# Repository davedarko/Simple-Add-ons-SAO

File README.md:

# Simple-Add-ons-SAO
Hardware Conference Badges tend to turn very complex, so to allow people to add bling and memes to their badge, the SAO (then shitty add-on) standard was developed. It started as a 2x2 header with two power pins and two I2C pins for data and a clock signal. Let me introduce you to the standard and show you what can be achieved. This is one of my favorite things to design, as they can be nice little gifts and inspires a lot of people for future years to also design and gift some. 

They are perfect gifts and spark joy!

Find all of my ~~shitty~~ simple add-ons in this repository. Plus some badges that were never converted to SAO but they still blink and everything.

## The current header - V1.69bis
The header was expanded to a 2x3 ISP connector later. Looking at the simple add-on, this is the layout.

## Designs in this repository

|Badge Name| Type | Eagle | Kicad | Description |
|----------|------|-------|-------|-------------|
| Ghibli/Soot Sprites | SAO | yes | - | A susuwatari simple add-on |
| LECCO postcard  | SAO | yes | - | Reminder token for a good time at Hackaday Europe 2026 in Lecco, Italy |
| Han SAOlo in carbonyte  | SAO | - | yes | work in progress, Attiny202 with RGB LEDs https://hackaday.io/project/197803-han-saolo|
| COVID-19 badge | SAO | - | yes | blinks with the help of a 555 timer on the back https://hackaday.io/project/187615-covid-19-sao-simple-add-on |
| "Hello my name is"  | SAO | - | yes | some blinks, some no https://hackaday.io/project/197693-hello-my-name-is-sao |
| MrAnderson  | SAO | - | yes | work in progress, hommage to Andy Anderson |
| Vendetta badge | SAO | - | yes | "remember, remember the 5th of November" - or anything else with the help of the little EEPROM on the back of this badge |
| Mr. Robot | SAO | yes | yes | with Attiny speaker https://hackaday.io/project/168037-mr-robot-shitty-addon |
| Penghito Poco | SAO | yes | - | small penghicorn badge |
| Do Or Donut | SAO | yes | - |  LED sprinkle matrix https://hackaday.io/project/168597-do-or-donut-sao |
| Knight Rider badge | SAO / pin | yes | yes | K.I.T.T. with animations thanks to an Attiny13 https://hackaday.io/project/25944-kitt-knight-rider-badgebrooch |
| sloth badge | pin | yes | - | inspired by some cute pimoroni pins, a sloth badge was formed https://hackaday.io/project/28330-sloth-badge |
| flux capacitor | pin | yes | - | with animations thanks to an Attiny13, the flux is flowing https://hackaday.io/project/25898-flux-capacitor-trinket|
| retro spacehuhn badge | pin | yes | - | RGB LED eyes on an olg Spacehuhn logo, with markers used for multicolor PCBs https://hackaday.io/project/33886-spacehuhn-badge |
| library stick  | other | yes | - | show off all your simple add-ons |

## Further designs

|Badge Name| Type | Eagle | Kicad | Description |
|----------|------|-------|-------|-------------|
| YoDawgSAO | SAO| - | yes| I heard you like badges on your badges? Here have some badges for your badges for your badges! https://github.com/davedarko/YoDawgSAO |
| T.A.R.S. | SAO| - | yes| Probably my most complex design, a small TARS with display and RP2040 https://github.com/davedarko/TARS-SAO |

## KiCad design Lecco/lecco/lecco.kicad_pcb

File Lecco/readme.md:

# Lecco, IT

First of all I'm so sorry for the footprint fail - the guy who gave a talk on how not to eff up the footprint, did exactly that, after making a whole bunch off addons.

You basically need an LED and a simple 2 row SMD header to make this work, but you have to botch the LED on it somehow.

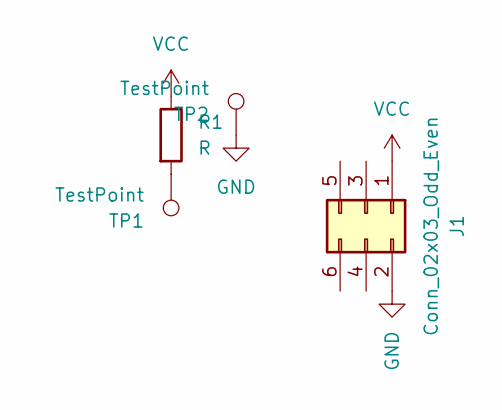
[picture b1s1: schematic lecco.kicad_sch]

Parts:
J1: Conn_02x03_Odd_Even; PinSocket_2x03_P2.54mm_Vertical_SMD
R1: R; R_0603_1608Metric_Pad0.98x0.95mm_HandSolder
TP1, TP2: TestPoint; TestPoint_Pad_D2.0mm

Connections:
GND: J1.2, TP2.1
unnamed: R1.2, TP1.1
VCC: J1.1, R1.1

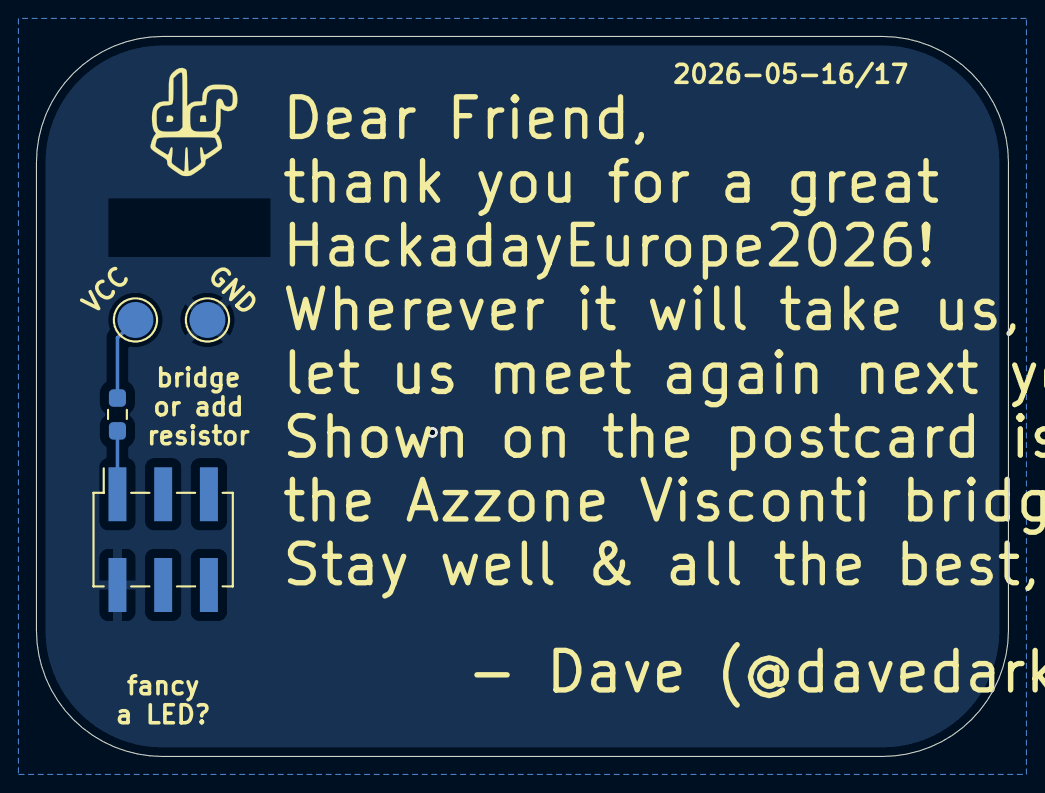
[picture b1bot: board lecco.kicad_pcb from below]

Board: 2 copper layers, 54.0 x 40.0 mm, 5 parts (5 on the bottom side), 3 nets.

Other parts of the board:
Ref**: Val**; davedarko_logo_silk_outline

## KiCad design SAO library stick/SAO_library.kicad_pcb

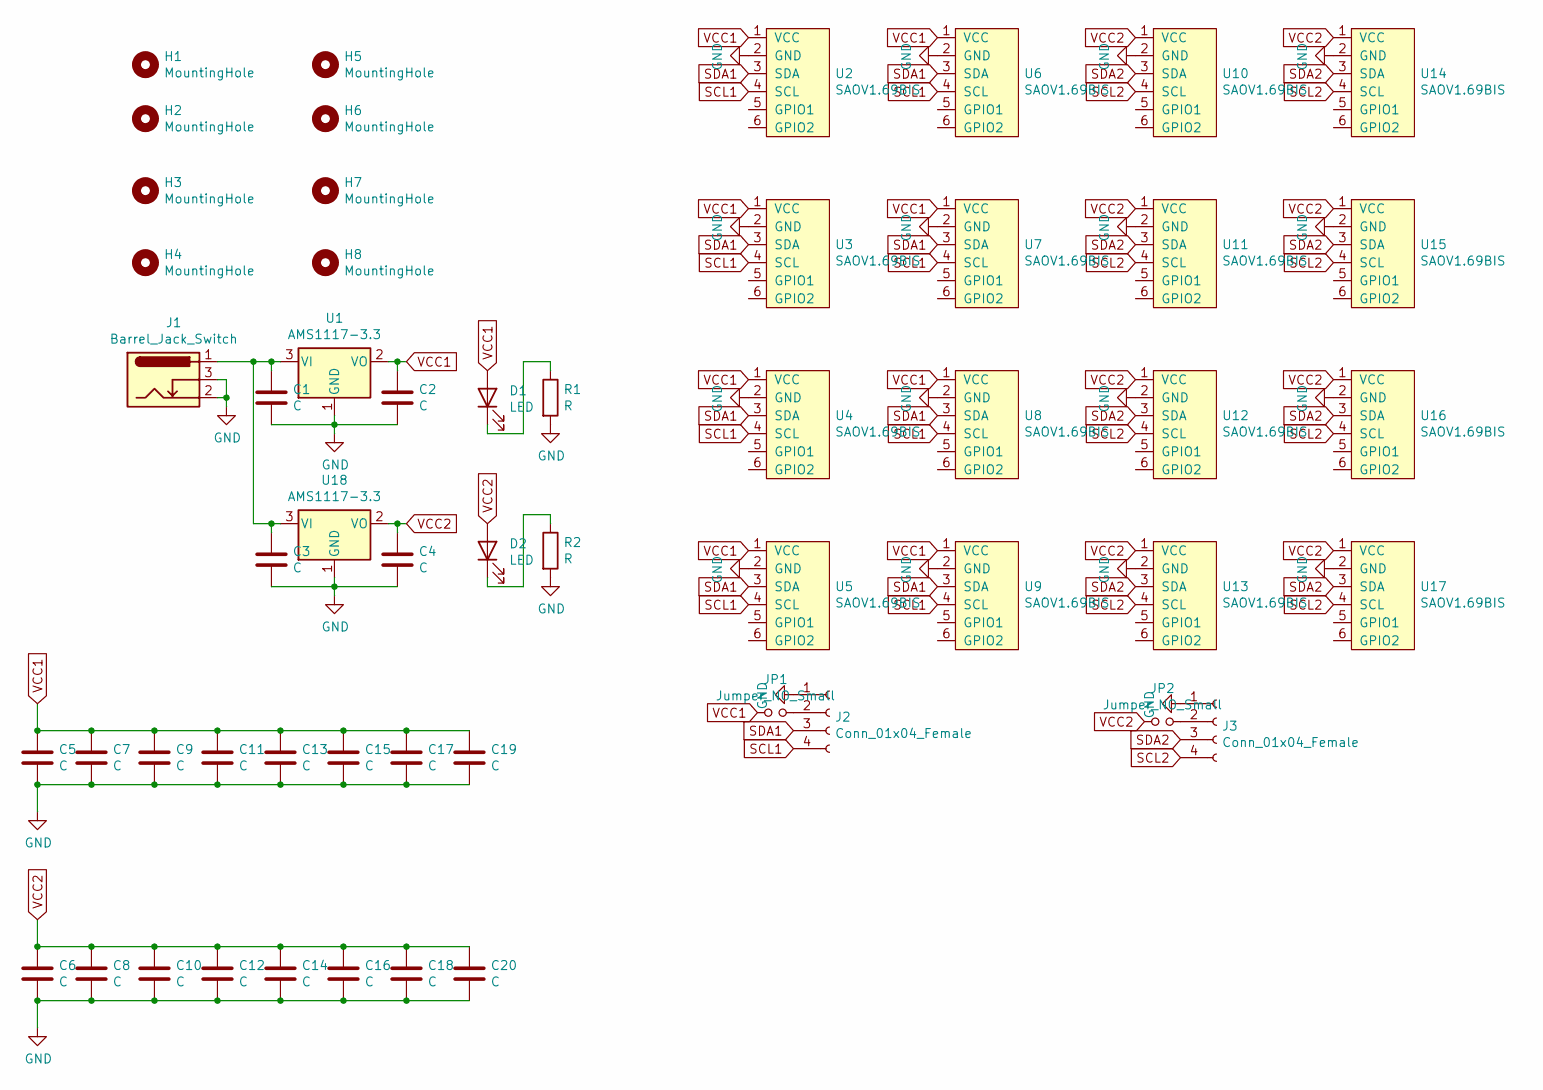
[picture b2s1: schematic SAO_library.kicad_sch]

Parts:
C1, C2, C3, C4, C5, C6, C7, C8, C9, C10, C11, C12, C13, C14, C15, C16, C17, C18, C19, C20: C; C_1206_3216Metric_Pad1.33x1.80mm_HandSolder
D1, D2: LED; LED_1206_3216Metric
H1, H2, H3, H4, H5, H6, H7, H8: MountingHole; MountingHole_3.2mm_M3_Pad_Via
J1: Barrel_Jack_Switch; BarrelJack_CUI_PJ-102AH_Horizontal
J2, J3: Conn_01x04_Female; JST_SH_SM04B-SRSS-TB_1x04-1MP_P1.00mm_Horizontal
JP1, JP2: Jumper_NO_Small; SolderJumper-2_P1.3mm_Open_RoundedPad1.0x1.5mm
R1, R2: R; R_1206_3216Metric_Pad1.30x1.75mm_HandSolder
U1, U18: AMS1117-3.3; SOT-223-3_TabPin2
U2, U3, U4, U5, U6, U7, U8, U9, U10, U11, U12, U13, U14, U15, U16, U17: SAOV1.69BIS; PinSocket_2x03_P2.54mm_Vertical

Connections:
GND: C1.2, C2.2, C3.2, C4.2, C5.2, C6.2, C7.2, C8.2, C9.2, C10.2, C11.2, C12.2, C13.2, C14.2, C15.2, C16.2, C17.2, C18.2, C19.2, C20.2, J1.2, J1.3, J2.1, J3.1, R1.2, R2.2, U1.1 (GND), U2.2 (GND), U3.2 (GND), U4.2 (GND), U5.2 (GND), U6.2 (GND), U7.2 (GND), U8.2 (GND), U9.2 (GND), U10.2 (GND), U11.2 (GND), U12.2 (GND), U13.2 (GND), U14.2 (GND), U15.2 (GND), U16.2 (GND), U17.2 (GND), U18.1 (GND)
unnamed: C1.1, C3.1, J1.1, U1.3 (VI), U18.3 (VI)
unnamed: D1.1 (K), R1.1
unnamed: D2.1 (K), R2.1
unnamed: J2.2, JP1.2
unnamed: J3.2, JP2.2
SCL1: J2.4, U2.4 (SCL), U3.4 (SCL), U4.4 (SCL), U5.4 (SCL), U6.4 (SCL), U7.4 (SCL), U8.4 (SCL), U9.4 (SCL)
SCL2: J3.4, U10.4 (SCL), U11.4 (SCL), U12.4 (SCL), U13.4 (SCL), U14.4 (SCL), U15.4 (SCL), U16.4 (SCL), U17.4 (SCL)
SDA1: J2.3, U2.3 (SDA), U3.3 (SDA), U4.3 (SDA), U5.3 (SDA), U6.3 (SDA), U7.3 (SDA), U8.3 (SDA), U9.3 (SDA)
SDA2: J3.3, U10.3 (SDA), U11.3 (SDA), U12.3 (SDA), U13.3 (SDA), U14.3 (SDA), U15.3 (SDA), U16.3 (SDA), U17.3 (SDA)
VCC1: C2.1, C5.1, C7.1, C9.1, C11.1, C13.1, C15.1, C17.1, C19.1, D1.2 (A), JP1.1, U1.2 (VO), U2.1 (VCC), U3.1 (VCC), U4.1 (VCC), U5.1 (VCC), U6.1 (VCC), U7.1 (VCC), U8.1 (VCC), U9.1 (VCC)
VCC2: C4.1, C6.1, C8.1, C10.1, C12.1, C14.1, C16.1, C18.1, C20.1, D2.2 (A), JP2.1, U10.1 (VCC), U11.1 (VCC), U12.1 (VCC), U13.1 (VCC), U14.1 (VCC), U15.1 (VCC), U16.1 (VCC), U17.1 (VCC), U18.2 (VO)

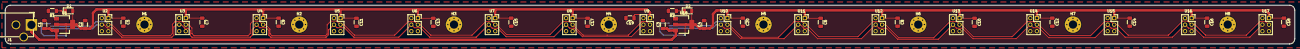
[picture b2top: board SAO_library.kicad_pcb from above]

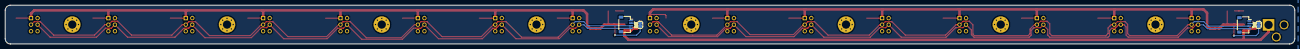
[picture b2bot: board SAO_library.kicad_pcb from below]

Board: 2 copper layers, 500.0 x 15.0 mm, 55 parts (4 on the bottom side), 12 nets.

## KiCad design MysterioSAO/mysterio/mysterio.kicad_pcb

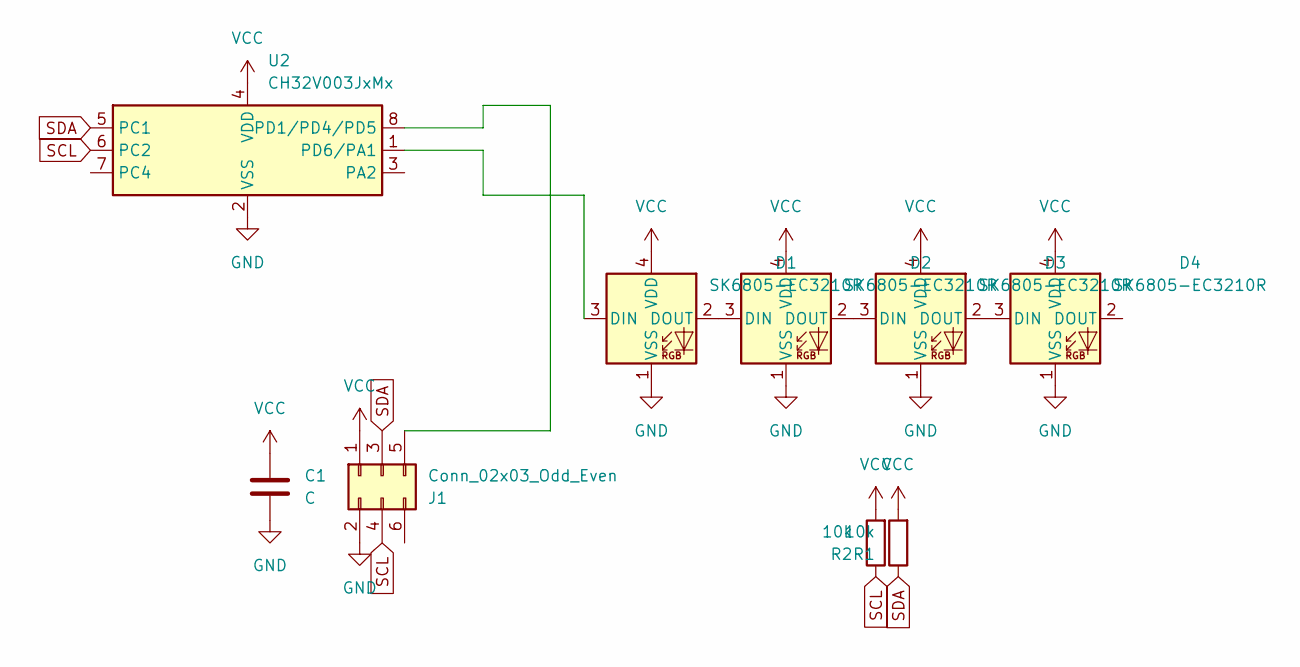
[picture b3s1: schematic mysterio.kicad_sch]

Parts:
C1: C; C_0603_1608Metric_Pad1.08x0.95mm_HandSolder
D1, D2, D3, D4: SK6805-EC3210R; LED_SK6805-EC3210R
J1: Conn_02x03_Odd_Even; IDC-Header_2x03_P2.54mm_Vertical
R1, R2: 10k; R_0603_1608Metric_Pad0.98x0.95mm_HandSolder
U2: CH32V003JxMx; SOP-8_3.9x4.9mm_P1.27mm

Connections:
GND: C1.2, D1.1 (VSS), D2.1 (VSS), D3.1 (VSS), D4.1 (VSS), J1.2, U2.2 (VSS)
unnamed: D1.3 (DIN), U2.1 (PD6/PA1)
unnamed: D1.2 (DOUT), D2.3 (DIN)
unnamed: D2.2 (DOUT), D3.3 (DIN)
unnamed: D3.2 (DOUT), D4.3 (DIN)
unnamed: J1.5, U2.8 (PD1/PD4/PD5)
SCL: J1.4, R2.1, U2.6 (PC2)
SDA: J1.3, R1.1, U2.5 (PC1)
VCC: C1.1, D1.4 (VDD), D2.4 (VDD), D3.4 (VDD), D4.4 (VDD), J1.1, R1.2, R2.2, U2.4 (VDD)

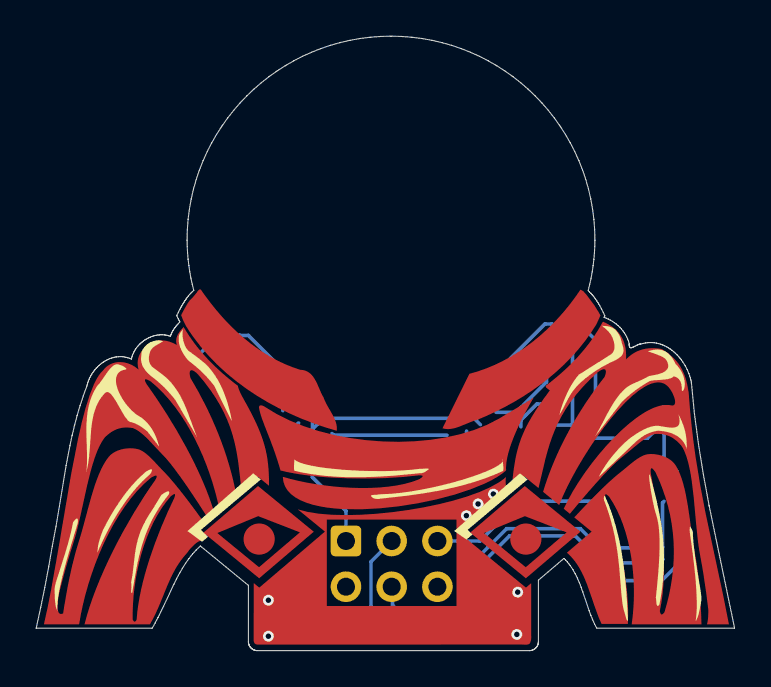
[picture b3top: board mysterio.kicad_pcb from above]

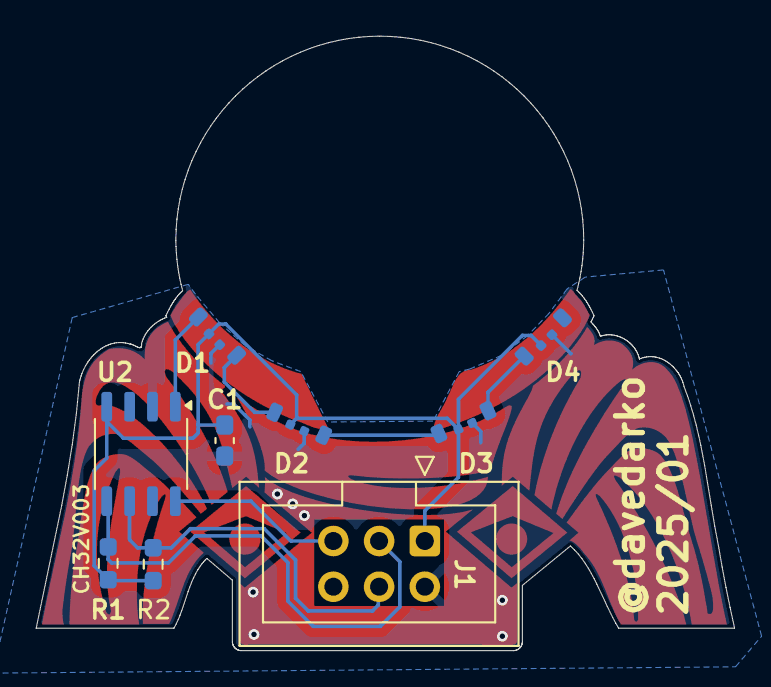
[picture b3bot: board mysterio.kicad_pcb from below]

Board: 4 copper layers, 38.8 x 34.1 mm, 9 parts (9 on the bottom side), 9 nets.

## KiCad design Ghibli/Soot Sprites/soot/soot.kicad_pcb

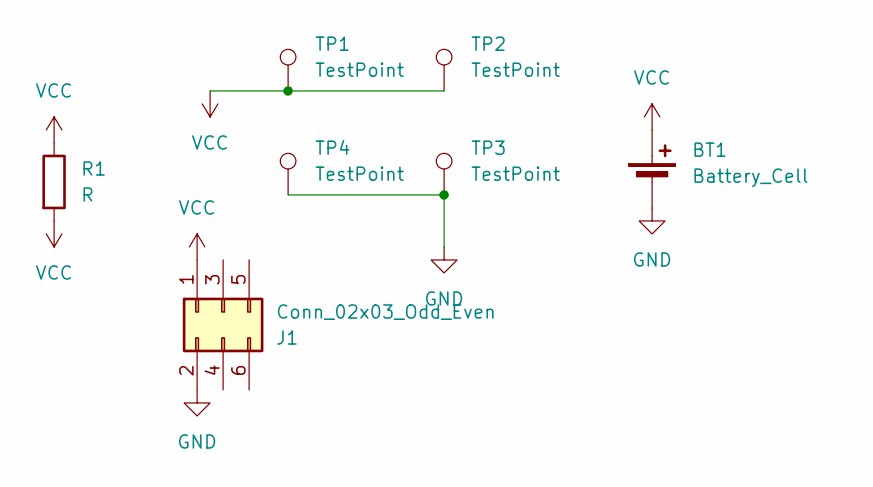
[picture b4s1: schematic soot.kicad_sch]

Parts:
BT1: Battery_Cell; BatteryHolder_Keystone_1060_1x2032
J1: Conn_02x03_Odd_Even; IDC-Header_2x03_P2.54mm_Vertical_SMD
R1: R; R_1206_3216Metric_Pad1.30x1.75mm_HandSolder
TP1, TP2, TP3, TP4: TestPoint; TestPoint_Pad_4.0x4.0mm

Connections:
GND: BT1.2 (-), J1.2, TP3.1, TP4.1
VCC: BT1.1 (+), J1.1, R1.1, R1.2, TP1.1, TP2.1

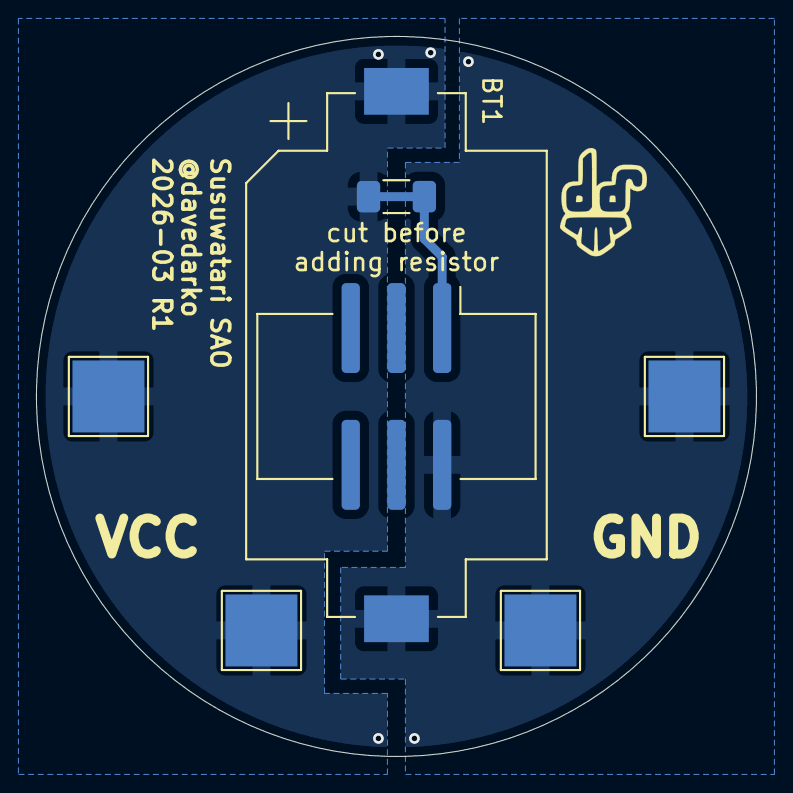
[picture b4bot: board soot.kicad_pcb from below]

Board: 2 copper layers, 40.0 x 40.0 mm, 8 parts (8 on the bottom side), 2 nets.

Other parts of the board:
Ref**: Val**; davedarko_logo_silk_outline

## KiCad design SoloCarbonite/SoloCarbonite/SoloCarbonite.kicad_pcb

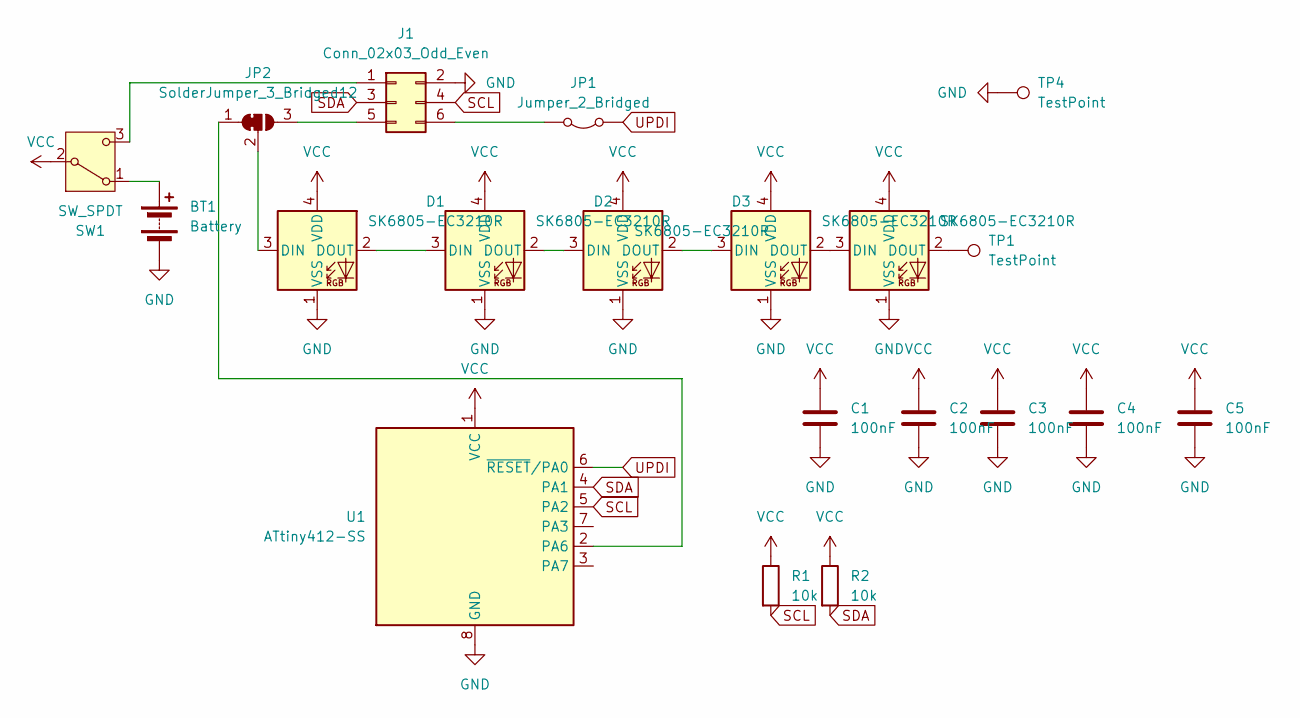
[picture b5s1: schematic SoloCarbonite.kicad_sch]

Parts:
BT1: Battery; Battery_holder_CR2023_BS-08-B2
C1, C2, C3, C4, C5: 100nF; C_0603_1608Metric_Pad1.08x0.95mm_HandSolder; MPN C14663
D1, D2, D3, D4, D5: SK6805-EC3210R; LED_SK6805-EC3210R; MPN C5378735
J1: Conn_02x03_Odd_Even; PinHeader_2x03_P2.54mm_Vertical; MPN DNP
JP1: Jumper_2_Bridged; SolderJumper-2_P1.3mm_Bridged_RoundedPad1.0x1.5mm; MPN DNP
JP2: SolderJumper_3_Bridged12; SolderJumper-3_P1.3mm_Bridged2Bar12_RoundedPad1.0x1.5mm; MPN DNP
R1, R2: 10k; R_0603_1608Metric_Pad0.98x0.95mm_HandSolder; MPN C25804
SW1: SW_SPDT; SW_SPDT_PCM12
TP1: TestPoint; TestPoint_Pad_D2.0mm; MPN DNP
TP4: TestPoint; TestPoint_Pad_D3.0mm; MPN DNP
U1: ATtiny412-SS; SOIC-8_3.9x4.9mm_P1.27mm; MPN C1337190

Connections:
GND: BT1.2 (-), C1.2, C2.2, C3.2, C4.2, C5.2, D1.1 (VSS), D2.1 (VSS), D3.1 (VSS), D4.1 (VSS), D5.1 (VSS), J1.2, TP4.1, U1.8 (GND)
unnamed: BT1.1 (+), SW1.1 (A)
unnamed: D1.3 (DIN), JP2.2 (C)
unnamed: D1.2 (DOUT), D2.3 (DIN)
unnamed: D2.2 (DOUT), D3.3 (DIN)
unnamed: D3.2 (DOUT), D4.3 (DIN)
unnamed: D4.2 (DOUT), D5.3 (DIN)
unnamed: D5.2 (DOUT), TP1.1
unnamed: J1.1, SW1.3 (C)
unnamed: J1.5, JP2.3 (B)
unnamed: J1.6, JP1.2 (B)
unnamed: JP2.1 (A), U1.2 (PA6)
SCL: J1.4, R1.2, U1.5 (PA2)
SDA: J1.3, R2.2, U1.4 (PA1)
UPDI: JP1.1 (A), U1.6 (~RESET/PA0)
VCC: C1.1, C2.1, C3.1, C4.1, C5.1, D1.4 (VDD), D2.4 (VDD), D3.4 (VDD), D4.4 (VDD), D5.4 (VDD), R1.1, R2.1, SW1.2 (B), U1.1 (VCC)

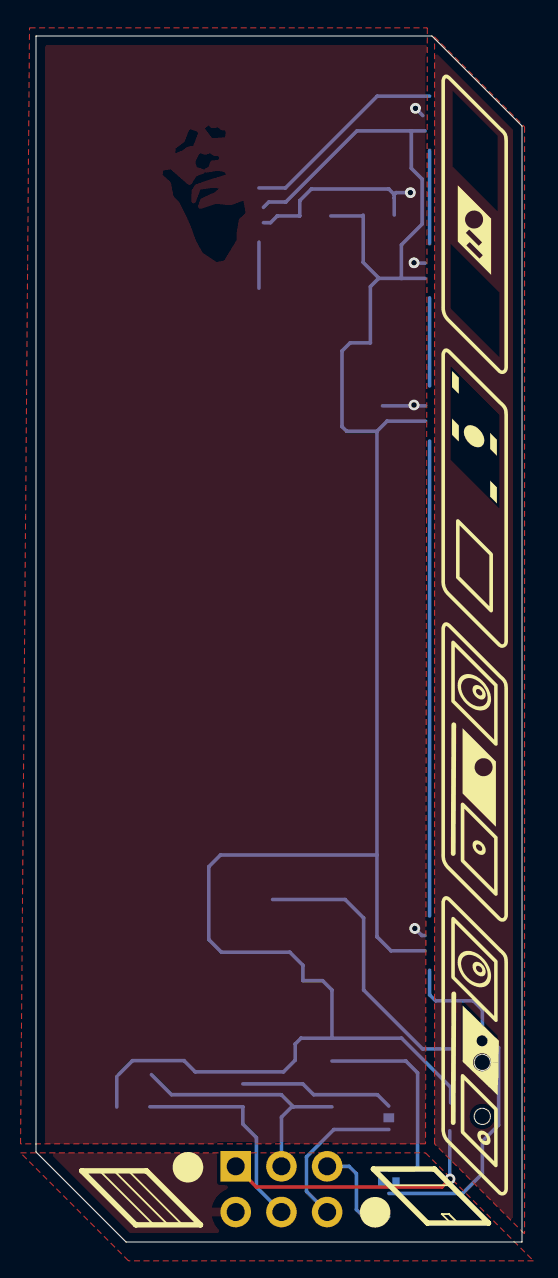
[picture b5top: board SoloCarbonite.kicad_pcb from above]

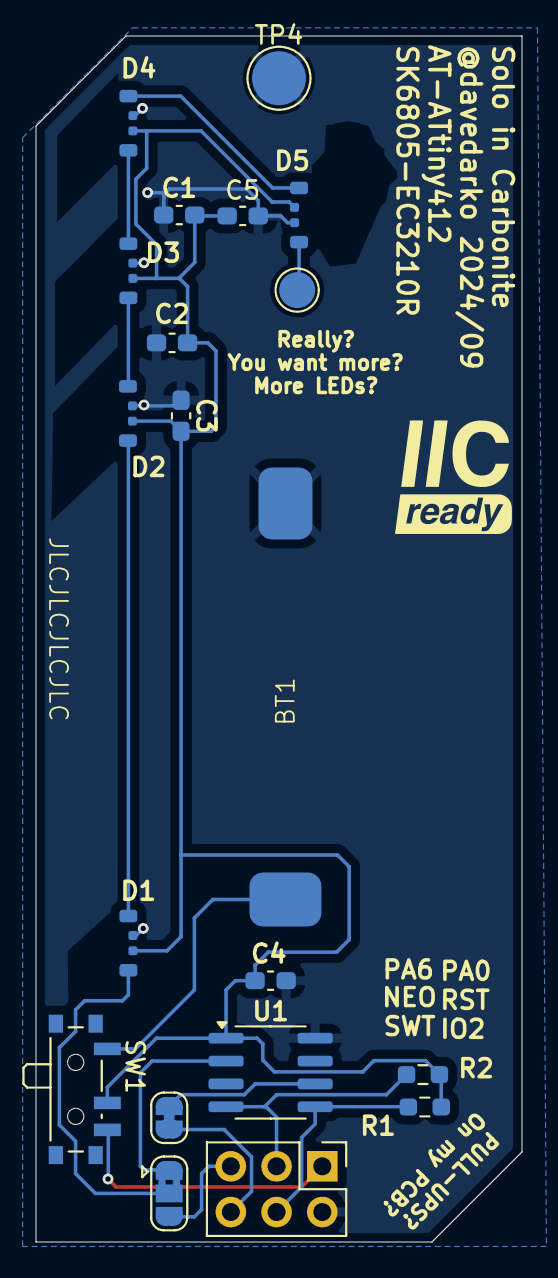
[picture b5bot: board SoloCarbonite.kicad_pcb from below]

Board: 2 copper layers, 27.0 x 67.0 mm, 20 parts (20 on the bottom side), 16 nets.

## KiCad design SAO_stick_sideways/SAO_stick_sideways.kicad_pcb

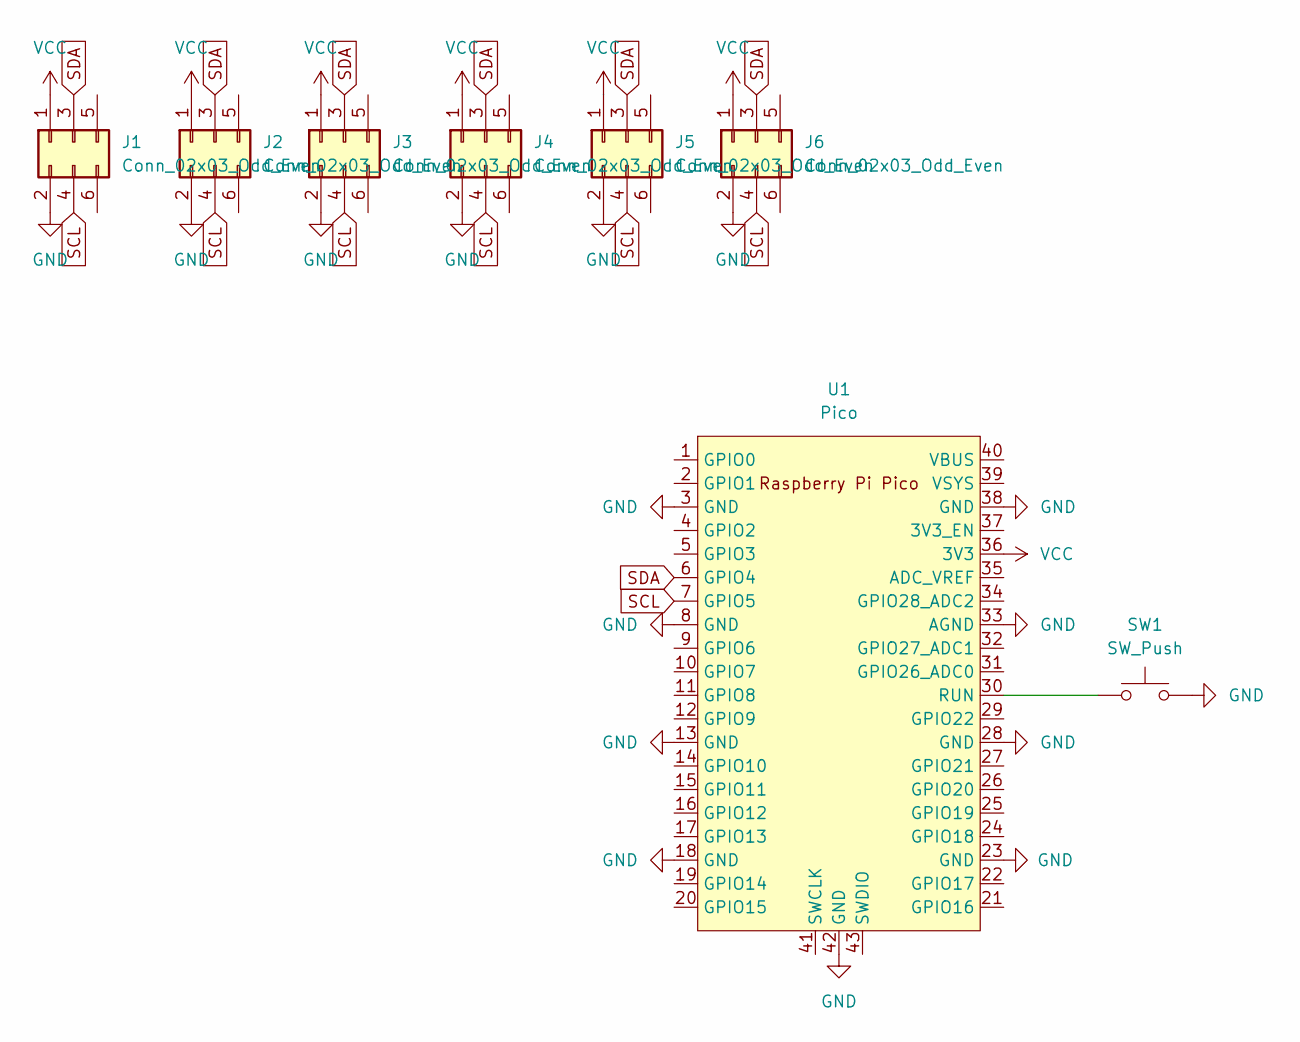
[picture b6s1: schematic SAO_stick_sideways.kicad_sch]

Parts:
J1, J6: Conn_02x03_Odd_Even; IDC-Header_2x03_P2.54mm_Vertical
J2, J3, J4, J5: Conn_02x03_Odd_Even; IDC-Header_2x03_P2.54mm_Vertical_SMD
SW1: SW_Push; SW_SPST_B3S-1000
U1: Pico; RPi_Pico_SMD_TH_no_silk

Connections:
GND: J1.2, J2.2, J3.2, J4.2, J5.2, J6.2, SW1.2, U1.3 (GND), U1.8 (GND), U1.13 (GND), U1.18 (GND), U1.23 (GND), U1.28 (GND), U1.33 (AGND), U1.38 (GND), U1.42 (GND)
unnamed: SW1.1, U1.30 (RUN)
SCL: J1.4, J2.4, J3.4, J4.4, J5.4, J6.4, U1.7 (GPIO5)
SDA: J1.3, J2.3, J3.3, J4.3, J5.3, J6.3, U1.6 (GPIO4)
VCC: J1.1, J2.1, J3.1, J4.1, J5.1, J6.1, U1.36 (3V3)

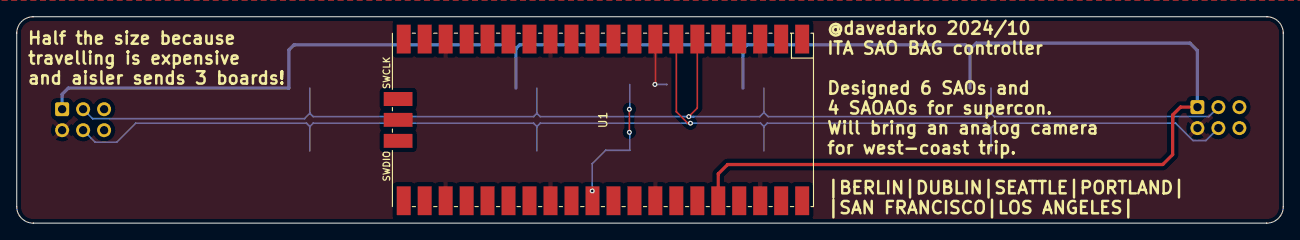
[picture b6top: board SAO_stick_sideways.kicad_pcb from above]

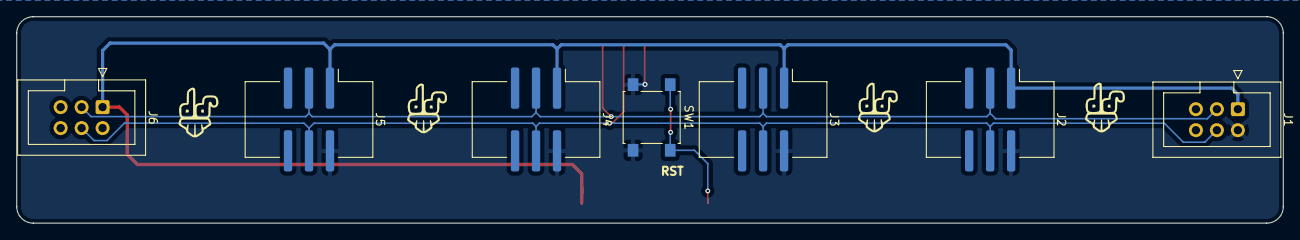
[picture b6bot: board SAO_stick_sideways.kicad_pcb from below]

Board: 2 copper layers, 153.4 x 25.0 mm, 12 parts (11 on the bottom side), 5 nets.

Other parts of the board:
Ref**: Val**; davedarko_logo_silk_outline
Ref**#2, Ref**#3, Ref**#4: Val**; davedarko_logo_silk_outline

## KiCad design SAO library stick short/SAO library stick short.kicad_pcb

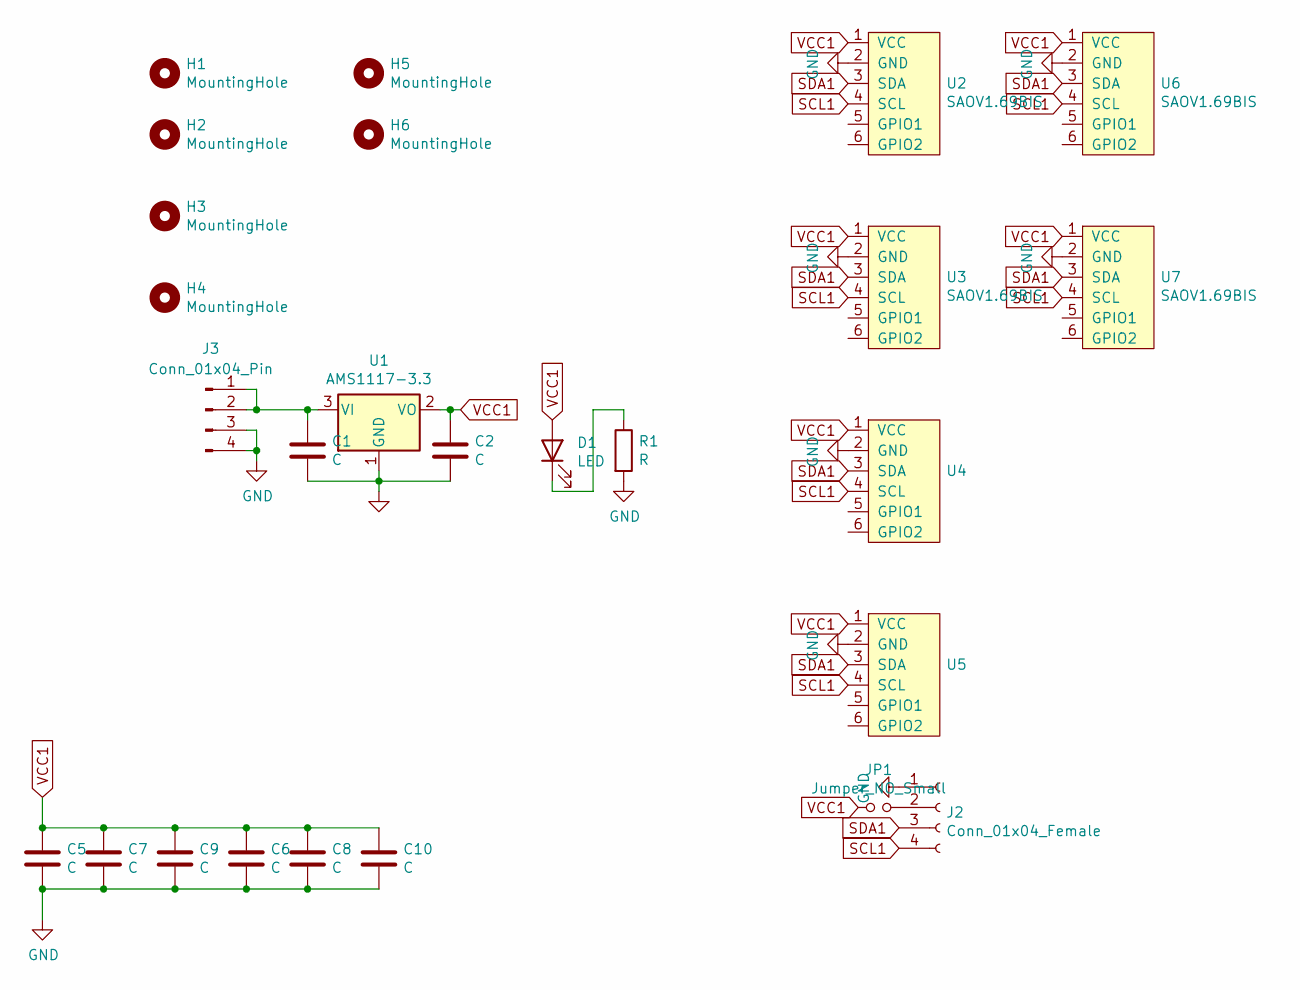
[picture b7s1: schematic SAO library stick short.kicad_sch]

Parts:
C1, C2, C5, C6, C7, C8, C9, C10: C; C_1206_3216Metric_Pad1.33x1.80mm_HandSolder
D1: LED; LED_1206_3216Metric
H1, H2, H3, H4, H5, H6: MountingHole; MountingHole_3.2mm_M3_Pad_Via
J2: Conn_01x04_Female; JST_SH_SM04B-SRSS-TB_1x04-1MP_P1.00mm_Horizontal
J3: Conn_01x04_Pin; PinSocket_1x04_P2.54mm_Vertical
JP1: Jumper_NO_Small; SolderJumper-2_P1.3mm_Open_RoundedPad1.0x1.5mm
R1: R; R_1206_3216Metric_Pad1.30x1.75mm_HandSolder
U1: AMS1117-3.3; SOT-223-3_TabPin2
U2, U3, U4, U5, U6, U7: SAOV1.69BIS; PinSocket_2x03_P2.54mm_Vertical

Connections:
GND: C1.2, C2.2, C5.2, C6.2, C7.2, C8.2, C9.2, C10.2, J2.1, J3.3, J3.4, R1.2, U1.1 (GND), U2.2 (GND), U3.2 (GND), U4.2 (GND), U5.2 (GND), U6.2 (GND), U7.2 (GND)
unnamed: D1.1 (K), R1.1
unnamed: J2.2, JP1.2
unnamed: C1.1, J3.1, J3.2, U1.3 (VI)
SCL1: J2.4, U2.4 (SCL), U3.4 (SCL), U4.4 (SCL), U5.4 (SCL), U6.4 (SCL), U7.4 (SCL)
SDA1: J2.3, U2.3 (SDA), U3.3 (SDA), U4.3 (SDA), U5.3 (SDA), U6.3 (SDA), U7.3 (SDA)
VCC1: C2.1, C5.1, C6.1, C7.1, C8.1, C9.1, C10.1, D1.2 (A), JP1.1, U1.2 (VO), U2.1 (VCC), U3.1 (VCC), U4.1 (VCC), U5.1 (VCC), U6.1 (VCC), U7.1 (VCC)

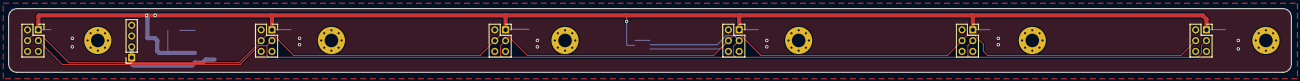
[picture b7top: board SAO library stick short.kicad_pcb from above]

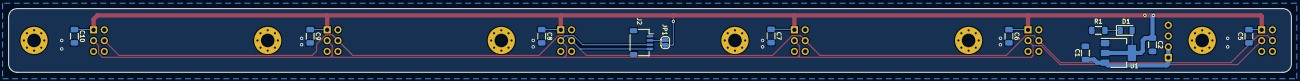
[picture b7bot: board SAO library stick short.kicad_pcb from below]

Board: 2 copper layers, 302.0 x 15.0 mm, 26 parts (13 on the bottom side), 7 nets.

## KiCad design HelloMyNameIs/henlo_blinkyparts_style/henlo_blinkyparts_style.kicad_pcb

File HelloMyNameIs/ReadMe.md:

# Hello My Name Is SAO
For their Supercon in 2024 a contest for simple add-ons was held by hackaday.
My first entry to this contest was a a simple name Tag design,
since programming badges can be overwhelming and the contest called for all sorts of cool stuff,
I saw this as my "pièce de résistance" project to warm up with KiCad again.

## errata
For the event I had ordered 3 boards each in green, red and blue. 
The blue version has the order number on the front.
All of them only have one of the LEDs correctly connected, for the other three you have to botch a bit.
But 1 LED seems plenty strong already anyways.

## files
There are two versions, but you're probably most interested in the LED version - that would be in the "blinkyparts style" folder.

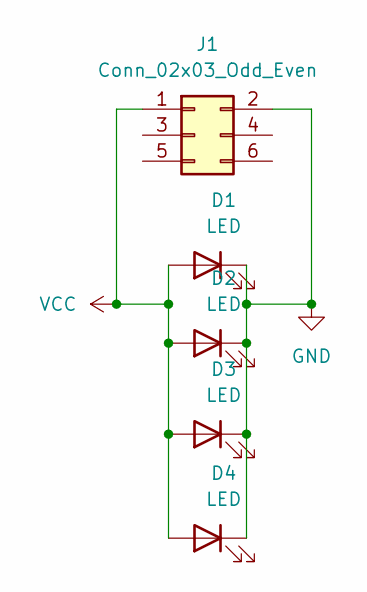
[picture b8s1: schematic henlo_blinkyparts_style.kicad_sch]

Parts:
D1, D2, D3, D4: LED; LED_1210_3225Metric_Pad1.42x2.65mm_HandSolder
J1: Conn_02x03_Odd_Even; IDC-Header_2x03_P2.54mm_Vertical

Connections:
GND: D1.1 (K), D2.1 (K), D3.1 (K), D4.1 (K), J1.2
VCC: D1.2 (A), D2.2 (A), D3.2 (A), D4.2 (A), J1.1
